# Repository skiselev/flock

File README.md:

# Flock
Floppy Disk Controller and Real Time Clock for RC2014 compatible systems

## Table of Content
* [Overview](#overview)
  * [Specifications](#specifications)
* [Assembly Instructions](#assembly-instructions)
* [Hardware Documentation](#hardware-documentation)
  * [Schematic and PCB Layout](#schematic-and-pcb-layout)
  * [Input/Output Ports](#inputoutput-ports)
  * [Connectors](#connectors)
  * [Bill of Materials](#bill-of-materials)
* [Release Notes](#release-notes)
  * [Changes](#changes)
  * [Known Issues](#known-issues)
* [Red Tape](#red-tape)
  * [Licensing](#licensing)
  * [Trademarks](#trademarks)

## Overview
Flock is an RC2014*-compatible floppy disk controller (FDC) and real time clock (RTC) module. It designed to work with RomWBW firmware, supporting CP/M, ZSDOS, and various applications under these OSes.

### Specifications
* Floppy Disk Controller: Western Digital* WD37C65 or compatible
  * NEC uPD765 compatible with an integrated data separator and floppy interface drivers and buffers
* Supported floppy disk formats:
  * 3.5", 720 KB
  * 3.5", 1.44 MB
  * 5.25", 360 KB (in 5.25", 360 KB drives only)
  * 5.25", 1.2 MB
* Supports two floppy drives, using IBM PC-like cable with twisted Disk Select / Motor Enable wires between two drives
* Real Time Clock: Maxim Integrated DS1302
* Bus: RC2014* compatible

## Assembly Instructions

Please refer to [Assembly Instructions](Assembly_Instructions.md) document

## Hardware Documentation

### Schematic and PCB Layout

[Schematic - Version 1.0](KiCad/Z80-FDC-Schematic-1.0.pdf)

[PCB Layout - Version 1.0](KiCad/Z80-FDC-Board-1.0.pdf)

### Input/Output Ports

Flock uses the following I/O ports:

#### 0x48 - FDC CCR/DIR

Write: Floppy disk controller control configuration register (CCR)
Read: Floppy disk controller digital input register (DIR)

#### 0x50 - FDC MSR

Read: Floppy disk controller master status register (MSR)

#### 0x51 - FDC Data Register

Read/Write: Data from/to floppy disk controller

#### 0x58 - FDC DOR / TC

Write: Floppy disk controller digital output register (DOR)
Read: Toggle floppy disk controller transfer complete (TC) line

#### 0xC0 - RTC

Read/Write: Access real time clock (RTC)

### Connectors

#### J1 - Floppy
Connect to floppy drive interface connector.

Pin   | Signal Name | Description | Pin   | Signal Name | Description
----- | ----------- | ------------| ----- | ----------- | -----------
J1-1  | GND         | Ground      | J1-2  | /DENSEL     | Density Select: 1 = Low density; 0 = High density
J1-3  | GND         | Ground      | J1-4  | N/C         | Not connected
J1-5  | GND         | Ground      | J1-6  | N/C         | Not connected
J1-7  | GND         | Ground      | J1-8  | /INDEX      | Index hole: 0 = At the index hole
J1-9  | GND         | Ground      | J1-10 | /MEA        | Motor Enable - Drive A
J1-11 | GND         | Ground      | J1-12 | /DSB        | Drive Select - Drive B
J1-13 | GND         | Ground      | J1-14 | /DSA        | Drive Select - Drive A
J1-15 | GND         | Ground      | J1-16 | /MEB        | Motor Enable - Drive B
J1-17 | GND         | Ground      | J1-18 | /DIR        | Direction Select
J1-19 | GND         | Ground      | J1-20 | /STEP       | Head Step
J1-21 | GND         | Ground      | J1-22 | /WDATA      | Write Data
J1-23 | GND         | Ground      | J1-24 | /WE         | Write Enable: 0 = Write Enabled
J1-25 | GND         | Ground      | J1-26 | /TRK0       | Track 00: 0 = At the track 0
J1-27 | GND         | Ground      | J1-28 | /WP         | Write Protect: 0 = Floppy disk is write protected
J1-29 | GND         | Ground      | J1-30 | /RDATA      | Read Data 
J1-31 | GND         | Ground      | J1-32 | /HDSEL      | Head Select / Side Select: 1 = Side 0; 0 = Side 1
J1-33 | GND         | Ground      | J1-34 | /DC         | Disk changed: 1 = Disk changed; 0 = Ready

#### J2 - Floppy 5V
Connect to floppy 5V power supply connector.

**Important: J2 is an unfused 5V power supply for a single 3.5" floppy disk drive. Avoid overloading and short-circuiting**

Pin | Signal Name | Description
--- | ----------- | -----------
1   | 5V          | Positive terminal - +5V
2   | GND         | Negative terminal - ground

#### J3, J4 - RC2014* Bus
Pin   | Signal Name | Description         | Pin  | Signal Name | Description
----- | ----------- | --------------------------------------- | ----- | ----------- | -----------
J3-1  | A15         | Address A15; Output                     |       |             |
J3-2  | A14         | Address A14; Output                     |       |             |
J3-3  | A13         | Address A13; Output                     |       |             |
J3-4  | A12         | Address A12; Output                     |       |             |
J3-5  | A11         | Address A11; Output                     |       |             |
J3-6  | A10         | Address A10; Output                     |       |             |
J3-7  | A9          | Address A9; Output                      |       |             |
J3-8  | A8          | Address A8; Output                      |       |             |
J3-9  | A7          | Address A7; Output                      |       |             |
J3-10 | A6          | Address A6; Output                      |       |             |
J3-11 | A5          | Address A5; Output                      |       |             |
J3-12 | A4          | Address A4; Output                      |       |             |
J3-13 | A3          | Address A3; Output                      |       |             |
J3-14 | A2          | Address A2; Output                      |       |             |
J3-15 | A1          | Address A1; Output                      |       |             |
J3-16 | A0          | Address A0; Output                      |       |             |
J3-17 | GND         | Ground                                  | J4-1  | GND         | Ground
J3-18 | VCC         | Power Supply - +5V                      | J4-2  | VCC         | Power Supply - +5V
J3-19 | /M1         | Machine Cycle One; Output               | J4-3  | /RFSH       | DRAM refresh; Output
J3-20 | /RESET      | Reset; Output                           | J4-4  | N/C         | Not connected
J3-21 | CLK1        | CPU Clock; Output                       | J4-5  | CLK2        | UART Clock (programmable); Output
J3-22 | /INT        | Interrupt; Input                        | J4-6  | /BUSACK     | DMA Bus Acknowledge; Output
J3-23 | /MREQ       | Memory Request; Output                  | J4-7  | /HALT       | Halt; Output
J3-24 | /WR         | Write Request; Output                   | J4-8  | /BUSREQ     | DMA Bus Request; Input
J3-25 | /RD         | Read Request; Output                    | J4-9  | /WAIT       | Wait; Input
J3-26 | /IORQ       | Input/Output Request; Output            | J4-10 | /NMI        | Non-maskable Interrupt; Input
J3-27 | D0          | Data D0; Input/Output                   |       |             |
J3-28 | D1          | Data D1; Input/Output                   |       |             |
J3-29 | D2          | Data D2; Input/Output                   |       |             |
J3-30 | D3          | Data D3; Input/Output                   |       |             |
J3-31 | D4          | Data D4; Input/Output                   |       |             |
J3-32 | D5          | Data D5; Input/Output                   |       |             |
J3-33 | D6          | Data D6; Input/Output                   |       |             |
J3-34 | D7          | Data D7; Input/Output                   |       |             |
J3-35 | TXDA        | Channel A, Transmit Data; Not Connected |       |             | 
J3-36 | RXDA        | Channel A, Receive Data; Not Connected  |       |             | 
J3-37 | USR1        | User Pin 1; Not connected               |       |             |
J3-38 | USR2        | User Pin 2; Not connected               |       |             |
J3-39 | USR3        | User Pin 3; Not connected               |       |             |

### Bill of Materials

#### Version 1.0

[Flock project on Mouser.com](https://www.mouser.com/ProjectManager/ProjectDetail.aspx?AccessID=5b60f70b94) - View and order all components except of the FDC and the PCB.

[Flock project on OSH Park](https://oshpark.com/shared_projects/BpUjKD43) - View and order the PCB.

Flock project on Tindie: [Complete kit](https://www.tindie.com/products/weird/flock-rc2014-compatible-module-kit/); [Flock PCB and FDC](https://www.tindie.com/products/weird/flock-rc2014-compatible-module-pcb-and-fdc/).

Component type     | Reference | Description                                 | Quantity | Possible sources and notes 
------------------ | --------- | ------------------------------------------- | -------- | --------------------------
PCB                |           | Flock PCB - Version 1.0                     | 1        | Buy from my Tindie store: [Complete kit](https://www.tindie.com/products/weird/flock-rc2014-compatible-module-kit/); [Flock PCB and FDC](https://www.tindie.com/products/weird/flock-rc2014-compatible-module-pcb-and-fdc/), or order from a PCB manufacturer of your choice using provided Gerber or KiCad files
Integrated Circuit | U1        | WD37C65BJM - FDC, CMOS, 44 pin PLCC         | 1        | eBay. Alternative: ST AIC37C65CL
Integrated Circuit | U2        | DS1302+ - RTC, 8 pin DIP                    | 1        | Mouser [700-DS1302](https://www.mouser.com/ProductDetail/700-DS1302)
Integrated Circuit | U3        | 74HCT174 - Hex D-type flip-flop with reset, 16 pin DIP | 1 | Mouser [595-CD74HCT174E](https://www.mouser.com/ProductDetail/595-CD74HCT174E)
Integrated Circuit | U4        | 74HCT138 - 3-Line to 8-Line decoders/demultiplexers, 16 pin DIP| 1 | Mouser [595-SN74HCT138NE4](https://www.mouser.com/ProductDetail/595-SN74HCT138NE4)
Integrated Circuit | U5        | 74HCT125 - Quadruple bus buffer gates with 3-state outputs, 14 pin DIP | 1 | Mouser [595-SN74HCT125NE4](https://www.mouser.com/ProductDetail/595-SN74HCT125NE4)
Integrated Circuit | U6        | 74HCT32 - Quadruple 2-input positive-OR gates, 14 pin DIP | 1 | Mouser [595-SN74HCT32NE4](https://www.mouser.com/ProductDetail/595-SN74HCT32NE4)
Quartz Crystal     | Y1        | 16 MHz, series                              | 1        | Mouser [774-ATS160-E](https://www.mouser.com/ProductDetail/774-ATS160-E)
Quartz Crystal     | Y2        | 32768 Hz, 6 pF                              | 1        | Mouser [815-AB26T32768KHZ6B](https://www.mouser.com/ProductDetail/815-AB26T32768KHZ6B)
Connector          | J1        | 2x17 pin header, shrouded, 2.54 mm pitch    | 1        | Mouser [517-30334-6002](https://www.mouser.com/ProductDetail/517-30334-6002); Alternative: Mouser [855-M20-9741746](https://www.mouser.com/ProductDetail/855-M20-9741746) (not shrouded, right angle)
Connector          | J2        | 2 pin header with friction lock, right angle | 1       | Mouser [571-2-644488-2](https://www.mouser.com/ProductDetail/571-2-644488-2)
Pin Header         | J3, J4    | 2x40 pin header, 2.54 mm pitch, right angle | 1        | Mouser [517-5121TG](https://www.mouser.com/ProductDetail/517-5121TG), or two [649-77315-118-16LF](https://www.mouser.com/ProductDetail/649-77315-118-16LF) and one [649-77317-104-20LF](https://www.mouser.com/ProductDetail/649-77317-104-20LF)
Capacitor          | C1 - C6   | 0.1 uF, 50V, MLCC, 5 mm pitch               | 6        | Mouser [810-FG28X7R1H104KNT6](https://www.mouser.com/ProductDetail/810-FG28X7R1H104KNT6)
Capacitor          | C7        | 10 uF, 63V, Organic Polymer, 6.3 mm diameter, 2.5 mm pitch | 1 | Mouser [80-A759EA106M1JAAE60](https://www.mouser.com/ProductDetail/80-A759EA106M1JAAE60)
Capacitor          | C8        | 0.22 F, 5.5V, Supercapacitor, 13.5 mm diameter, 5 mm pitch | 1 | Mouser [555-DBN-5R5D334T](https://www.mouser.com/ProductDetail/555-DBN-5R5D334T)
Capacitor          | C9        | 47 pF, 50V, MLCC, 5 mm pitch                | 6        | Mouser [810-FG28C0G2A470JNT0](https://www.mouser.com/ProductDetail/810-FG28C0G2A470JNT0)
Capacitor          | C10       | 15 pF, 50V, MLCC, 5 mm pitch                | 6        | Mouser [810-FG28C0G2A150JNT0](https://www.mouser.com/ProductDetail/810-FG28C0G2A150JNT0)
Resistor Array     | RN1       | 1 kohm, bussed, 6 pin SIP                   | 1        | Mouser [652-4606X-1LF-1K](https://www.mouser.com/ProductDetail/652-4606X-1LF-1K)
Resistor           | R1,  R2   | 4.7 kohm, 0.25 W, 1% tolerance, axial       | 2        | Mouser [603-MFR-25FRF52-4K7](https://www.mouser.com/ProductDetail/603-MFR-25FRF52-4K7)
IC Socket          | U1        | 44 pin PLCC, through hole                   | 1        | Mouser [517-8444-11B1-RK-TP](https://www.mouser.com/ProductDetail/517-8444-11B1-RK-TP)
IC Socket          | U2        | 8 pin DIP                                   | 1        | Mouser [649-DILB8P223TLF](https://www.mouser.com/ProductDetail/649-DILB8P223TLF)
IC Socket          | U3, U4    | 16 pin DIP                                  | 1        | Mouser [649-DILB16P-223TLF](https://www.mouser.com/ProductDetail/649-DILB16P-223TLF)
IC Socket          | U5, U6    | 14 pin DIP                                  | 1        | Mouser [649-DILB14P-223TLF](https://www.mouser.com/ProductDetail/649-DILB14P-223TLF)
Connector          | J2        | 2 pin connector                             | 1        | Mouser [571-3-643813-2](https://www.mouser.com/ProductDetail/571-3-643813-2)
Connector          | J2        | Floppy disk power connector housing         | 1        | Mouser [571-1718224](https://www.mouser.com/ProductDetail/571-1718224)
Connector          | J2        | Floppy disk power connector contacts        | 2        | Mouser [571-170262-2-LP](https://www.mouser.com/ProductDetail/571-170262-2-LP), [571-1702622-CT](https://www.mouser.com/ProductDetail/571-1702622-CT) (strip of 100 contacts)

## Release Notes

### Changes

* Version 1.0
  * Initial version

### Known Issues

* Version 1.0
  * No known issues

### Wishlist
* None so far

## Red Tape

### Licensing

Flock is an open source hardware project certified by [Open Source Hardware Association](https://www.oshwa.org/), certification UID is [US002115](https://certification.oshwa.org/us002115.html). The hardware design itself, including schematic and PCB layout design files are licensed under the strongly-reciprocal variant of [CERN Open Hardware Licence version 2](license-cern_ohl_s_v2.txt). The CPLD VHDL code is licensed under [GNU General Public License v3](license-gpl-3.0.txt). Documentation, including this file, is licensed under the [Creative Commons Attribution-ShareAlike 4.0 International License](license-cc-by-sa-4.0.txt).

### Trademarks

* "RC2014" is a registered trademark of RFC2795 Ltd.
* Other names and brands may be claimed as the property of others.

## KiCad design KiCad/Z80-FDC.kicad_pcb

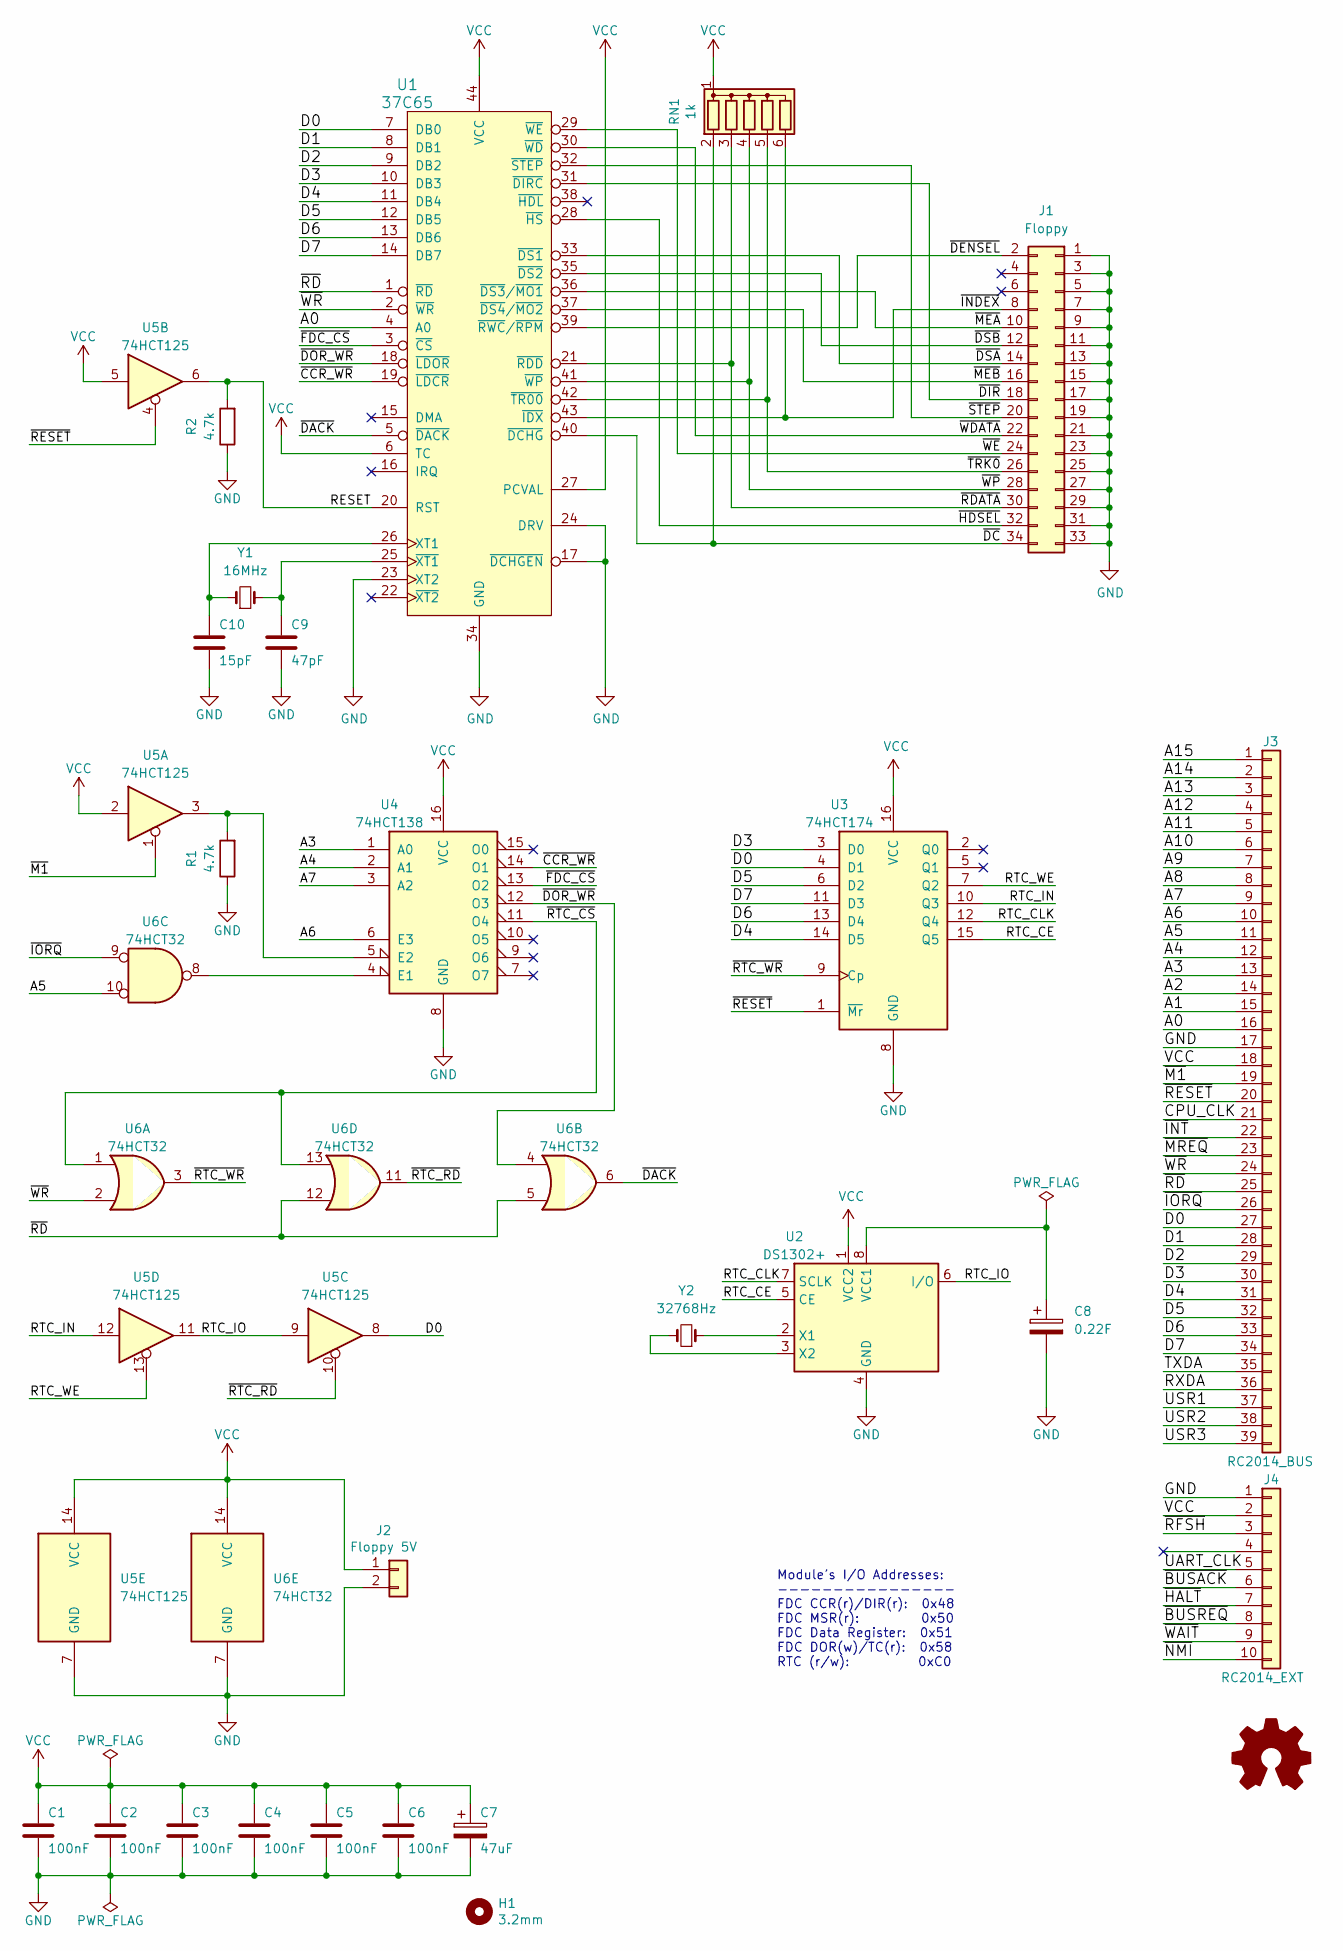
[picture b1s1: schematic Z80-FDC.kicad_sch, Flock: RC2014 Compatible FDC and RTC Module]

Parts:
C1, C2, C3, C4, C5, C6: 100nF; Cap_Cer_508
C7: 47uF; Cap_Elec_Radial_6.3mm
C8: 0.22F; Cap_Super_Radial_13.5mm
C9: 47pF; Cap_Cer_508
C10: 15pF; Cap_Cer_508
H1: 3.2mm; MountingHole_3.2mm_M3_DIN965
J1: Floppy; Conn_Pin_Header_17x2_2.54mm_Shrouded
J2: Floppy 5V; Conn_TE_2-644488-2_2P_2.54mm
J3: RC2014_BUS; Conn_Pin_Header_39x1_2.54mm_Right_Angle
J4: RC2014_EXT; Conn_Pin_Header_10x1_2.54mm_Right_Angle
LOGO1: Logo_Open_Hardware_Small; OSHW-Logo_5.7x6mm_SilkScreen
R1, R2: 4.7k; Res_762
RN1: 1k; Conn_SIL6
U1: 37C65; IC_PLCC44_TH
U2: DS1302+; IC_DIP8_300
U3: 74HCT174; IC_DIP16_300
U4: 74HCT138; IC_DIP16_300
U5: 74HCT125; IC_DIP14_300
U6: 74HCT32; IC_DIP14_300
Y1: 16MHz; Crystal_HC-49U_Vert
Y2: 32768Hz; Crystal_32K_Horiz

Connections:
/A0: J3.16, U1.4 (A0)
/A1: J3.15
/A2: J3.14
/A3: J3.13, U4.1 (A0)
/A4: J3.12, U4.2 (A1)
/A5: J3.11, U6.10
/A6: J3.10, U4.6 (E3)
/A7: J3.9, U4.3 (A2)
/A8: J3.8
/A9: J3.7
/A10: J3.6
/A11: J3.5
/A12: J3.4
/A13: J3.3
/A14: J3.2
/A15: J3.1
/CPU_CLK: J3.21
/D0: J3.27, U1.7 (DB0), U3.4 (D1), U5.8
/D1: J3.28, U1.8 (DB1)
/D2: J3.29, U1.9 (DB2)
/D3: J3.30, U1.10 (DB3), U3.3 (D0)
/D4: J3.31, U1.11 (DB4), U3.14 (D5)
/D5: J3.32, U1.12 (DB5), U3.6 (D2)
/D6: J3.33, U1.13 (DB6), U3.13 (D4)
/D7: J3.34, U1.14 (DB7), U3.11 (D3)
/RESET: R2.2, U1.20 (RST), U5.6
/RTC_CE: U2.5 (CE), U3.15 (Q5)
/RTC_CLK: U2.7 (SCLK), U3.12 (Q4)
/RTC_IN: U3.10 (Q3), U5.12
/RTC_IO: U2.6 (I/O), U5.9, U5.11
/RTC_WE: U3.7 (Q2), U5.13
/RXDA: J3.36
/TXDA: J3.35
/UART_CLK: J4.5
/USR1: J3.37
/USR2: J3.38
/USR3: J3.39
/~BUSACK: J4.6
/~BUSREQ: J4.8
/~CCR_WR: U1.19 (~LDCR), U4.14 (O1)
/~DACK: U1.5 (~DACK), U6.6
/~DC: J1.34, RN1.2 (R1), U1.40 (~DCHG)
/~DENSEL: J1.2, U1.39 (~RWC/~RPM)
/~DIR: J1.18, U1.31 (~DIRC)
/~DOR_WR: U1.18 (~LDOR), U4.12 (O3), U6.4
/~DSA: J1.14, U1.33 (~DS1)
/~DSB: J1.12, U1.35 (~DS2)
/~FDC_CS: U1.3 (~CS), U4.13 (O2)
/~HALT: J4.7
/~HDSEL: J1.32, U1.28 (~HS)
/~INDEX: J1.8, RN1.6 (R5), U1.43 (~IDX)
/~INT: J3.22
/~IORQ: J3.26, U6.9
/~M1: J3.19, U5.1
/~MEA: J1.10, U1.36 (~DS3/~MO1)
/~MEB: J1.16, U1.37 (~DS4/~MO2)
/~MREQ: J3.23
/~NMI: J4.10
/~RDATA: J1.30, RN1.3 (R2), U1.21 (~RDD)
/~RD: J3.25, U1.1 (~RD), U6.5, U6.12
/~RESET: J3.20, U3.1 (~Mr), U5.4
/~RFSH: J4.3
/~RTC_CS: U4.11 (O4), U6.1, U6.13
/~RTC_RD: U5.10, U6.11
/~RTC_WR: U3.9 (Cp), U6.3
/~STEP: J1.20, U1.32 (~STEP)
/~TRK0: J1.26, RN1.5 (R4), U1.42 (~TR00)
/~WAIT: J4.9
/~WDATA: J1.22, U1.30 (~WD)
/~WE: J1.24, U1.29 (~WE)
/~WP: J1.28, RN1.4 (R3), U1.41 (~WP)
/~WR: J3.24, U1.2 (~WR), U6.2
GND: C1.2, C2.2, C3.1, C4.2, C5.2, C6.2, C7.2, C8.2, C9.2, C10.2, J1.1, J1.3, J1.5, J1.7, J1.9, J1.11, J1.13, J1.15, J1.17, J1.19, J1.21, J1.23, J1.25, J1.27, J1.29, J1.31, J1.33, J2.2, J3.17, J4.1, R1.1, R2.1, U1.17 (~DCHGEN), U1.23 (XT2), U1.24 (DRV), U1.34 (GND), U2.4 (GND), U3.8 (GND), U4.8 (GND), U5.7 (GND), U6.7 (GND)
unnamed: C8.1, U2.8 (VCC1)
unnamed: C9.1, U1.25 (~XT1), Y1.2
unnamed: C10.1, U1.26 (XT1), Y1.1
unnamed: R1.2, U4.5 (E2), U5.3
unnamed: U2.2 (X1), Y2.1
unnamed: U2.3 (X2), Y2.2
unnamed: U4.4 (E1), U6.8
VCC: C1.1, C2.1, C3.2, C4.1, C5.1, C6.1, C7.1, J2.1, J3.18, J4.2, RN1.1 (common), U1.6 (TC), U1.27 (PCVAL), U1.44 (VCC), U2.1 (VCC2), U3.16 (VCC), U4.16 (VCC), U5.2, U5.5, U5.14 (VCC), U6.14 (VCC)

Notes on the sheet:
Module's I/O Addresses: ---------------- FDC CCR(r)/DIR(r): 0x48 FDC MSR(r): 0x50 FDC Data Register: 0x51 FDC DOR(w)/TC(r): 0x58 RTC (r/w): 0xC0

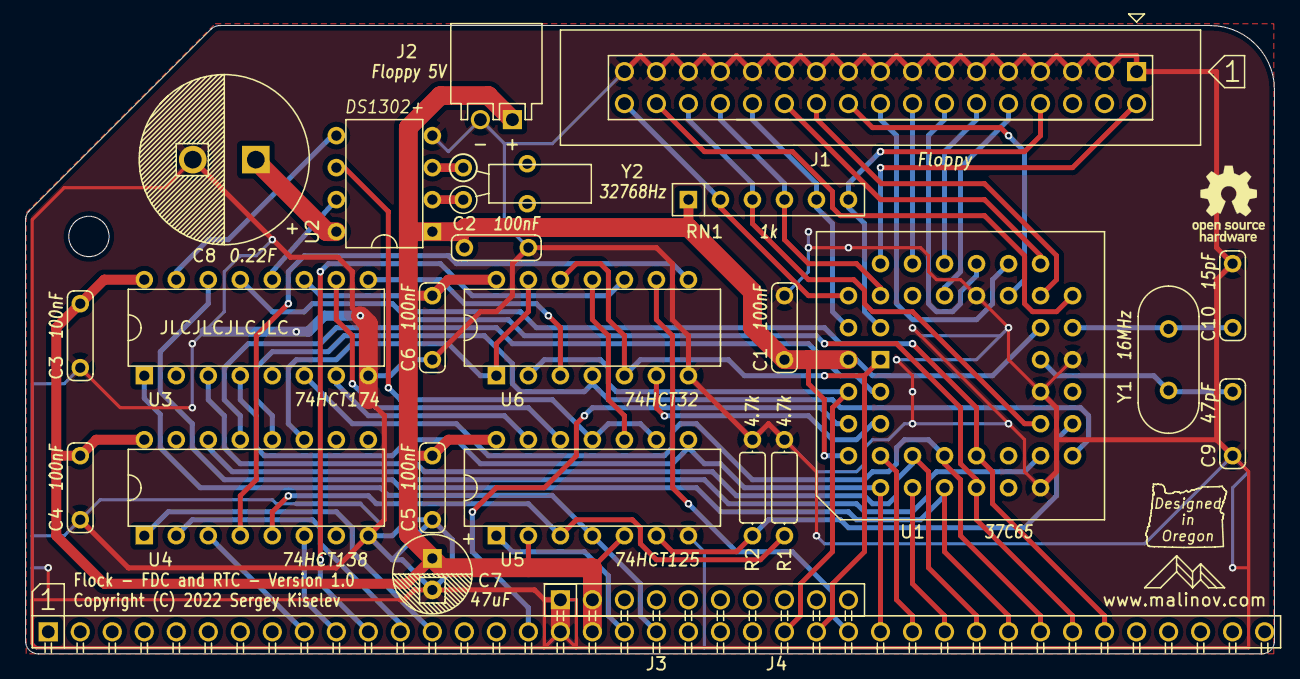
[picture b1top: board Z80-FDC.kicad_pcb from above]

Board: 2 copper layers, 99.1 x 49.9 mm, 28 parts (1 on the bottom side), 56 nets.

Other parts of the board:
LOGO1#2: Logo_Open_Hardware_Small; OSHW-Logo_5.7x6mm_SilkScreen

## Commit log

2022-05-24 Add images
2022-06-03 Add OSHWA ID
2022-06-06 Add pre-built ROM image with floppy disks support
2022-06-14 Add pictures for components
2023-02-18 Update Assembly_Instructions.md
    Added information that you can safely extract pin 3 from J1 to accommodate keyed cables.
2023-02-18 Update Assembly_Instructions.md
    Added information for FAT floppy formatting.

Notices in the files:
KiCad/Z80-FDC.kicad_pcb:
Licensed under CERN-OHL-S: https://cern-ohl.web.cern.ch
Copyright (C) 2022 Sergey Kiselev
README.md:
CERN-OHL-2.0-S, GPL-3.0, CC-BY-SA-4.0
